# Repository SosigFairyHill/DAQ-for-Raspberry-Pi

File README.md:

Schematic and board created in Eagle. The DAC and ADC chips were surface mount, so I used surface mount to DIP converters bought from SparkFun.

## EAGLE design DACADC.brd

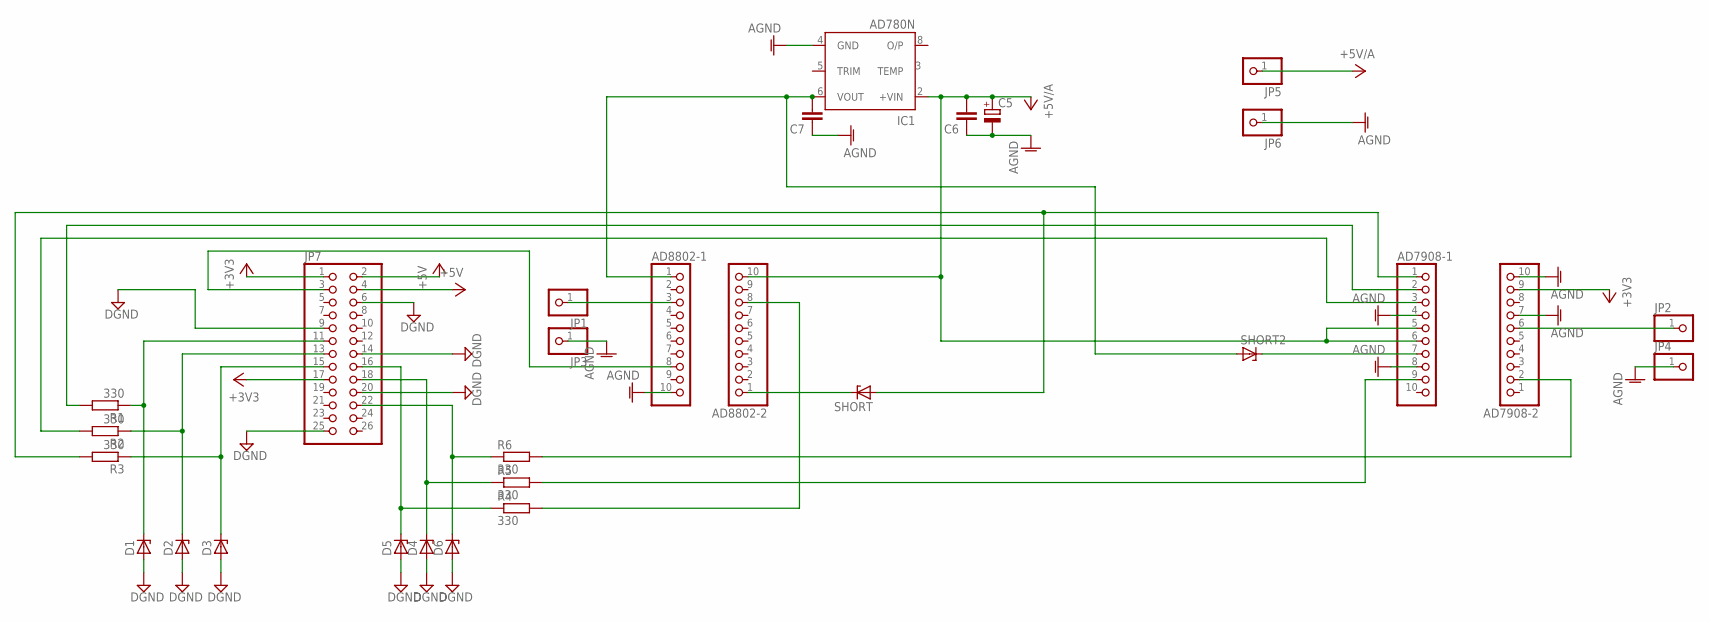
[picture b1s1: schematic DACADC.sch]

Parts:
AD7908-1, AD7908-2, AD8802-1, AD8802-2: PINHD-1X10; 1X10
C5: CPOL-EUE2.5-5; E2,5-5
C6, C7: C-EU025-030X050; C025-030X050
D1, D2, D3, D4, D5, D6: ZENER-DIODEDO34-7; DO34Z7
IC1: AD780N; DIL08
JP1, JP2, JP3, JP4, JP5, JP6: PINHD-1X1; 1X01
JP7: PINHD-2X13; 2X13
R1, R2, R3, R4, R5, R6: 330; 0204/5
SHORT, SHORT2: ZENER-DIODEDO34-7; DO34Z7

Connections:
+3V3: AD7908-2.9, JP7.1, JP7.17
+5V: JP7.2, JP7.4
+5V/A: AD7908-1.5, AD7908-1.6, AD8802-2.10, C5.+, C6.2, JP5.1
AGND: AD7908-1.4, AD7908-1.8, AD7908-2.7, AD7908-2.10, AD8802-1.10, C5.-, C6.1, C7.1, IC1.4 (GND), JP3.1, JP4.1, JP6.1
DGND: D1.A, D2.A, D3.A, D4.A, D5.A, D6.A, JP7.6, JP7.9, JP7.14, JP7.20, JP7.25
unnamed: D2.C, JP7.13, R2.1
unnamed: D3.C, JP7.15, R3.1
unnamed: D6.C, JP7.22, R6.1
unnamed: D4.C, JP7.18, R5.1
unnamed: D5.C, JP7.16, R4.1
unnamed: AD7908-1.2, R1.2
unnamed: AD7908-1.7, SHORT2.C
unnamed: AD7908-1.1, R3.2, SHORT.A
unnamed: AD7908-1.3, R2.2
unnamed: AD8802-2.8, R4.2
unnamed: AD7908-1.9, R5.2
unnamed: AD7908-2.2, R6.2
unnamed: AD8802-1.1, C7.2, IC1.6 (VOUT), SHORT2.A
unnamed: AD7908-2.6, JP2.1
unnamed: AD8802-1.3, JP1.1
unnamed: AD8802-1.8, JP7.3
unnamed: D1.C, JP7.11, R1.1
unnamed: AD8802-2.1, SHORT.C

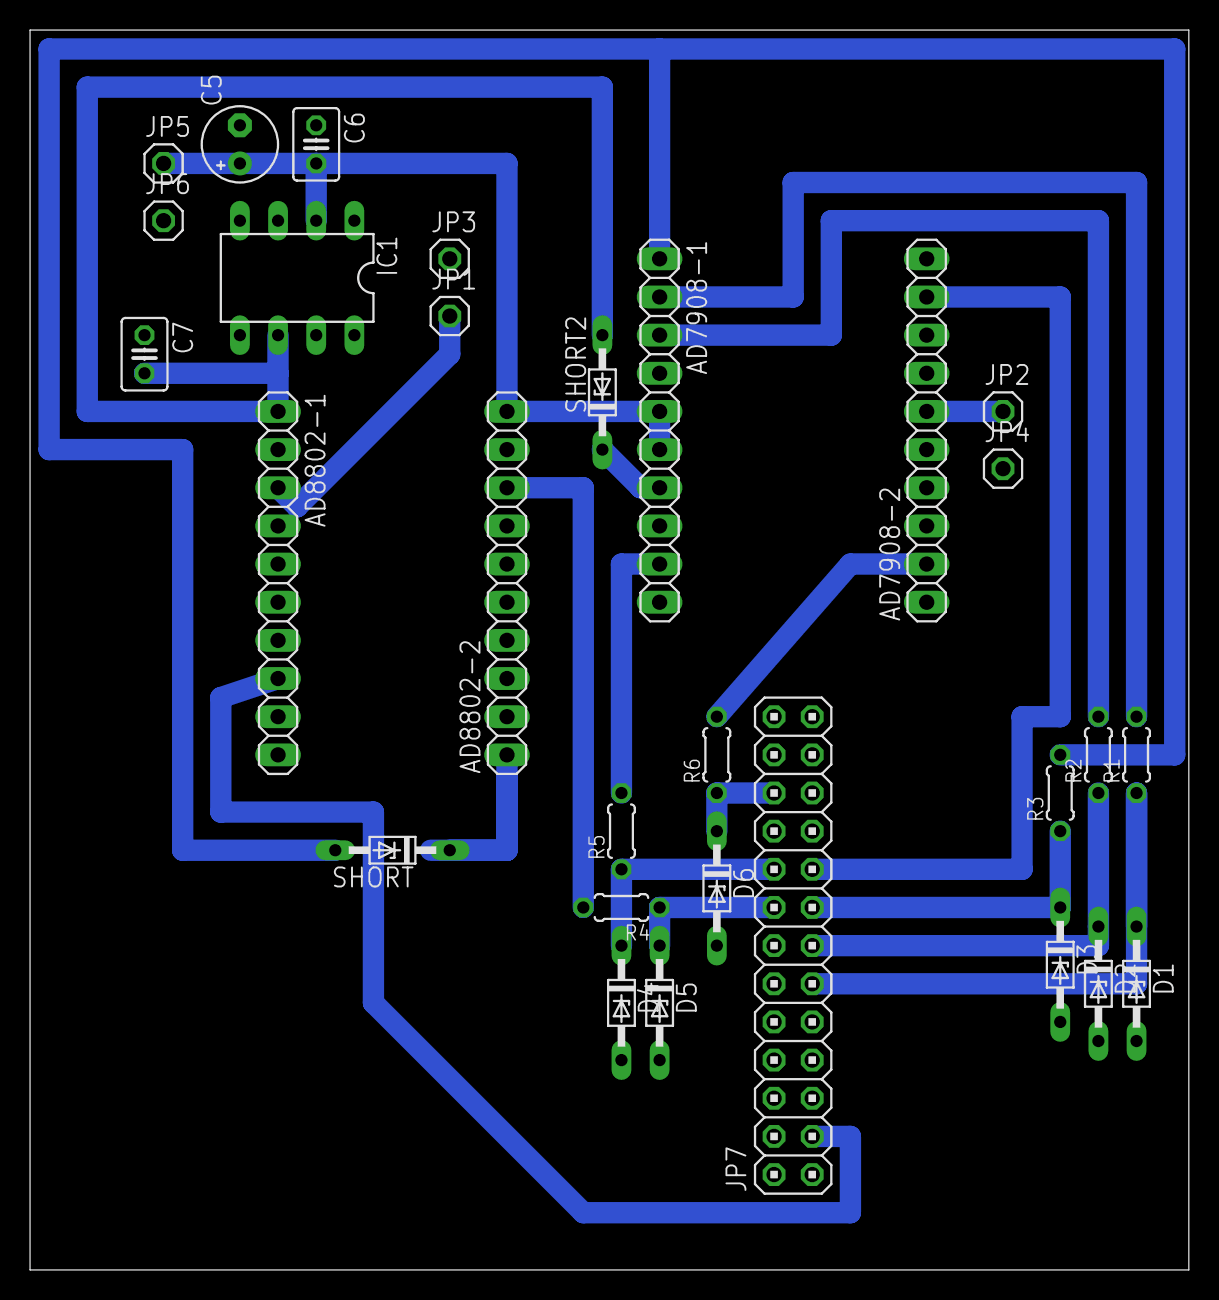
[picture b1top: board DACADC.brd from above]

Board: 2 copper layers, 77.1 x 82.5 mm, 29 parts (0 on the bottom side), 23 nets.

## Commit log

2014-11-28 add python scripts for the adc and dac
